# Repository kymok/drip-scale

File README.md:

# drip-scale
A drip scale which measures amount of water added and liquid extracted simultaneously.

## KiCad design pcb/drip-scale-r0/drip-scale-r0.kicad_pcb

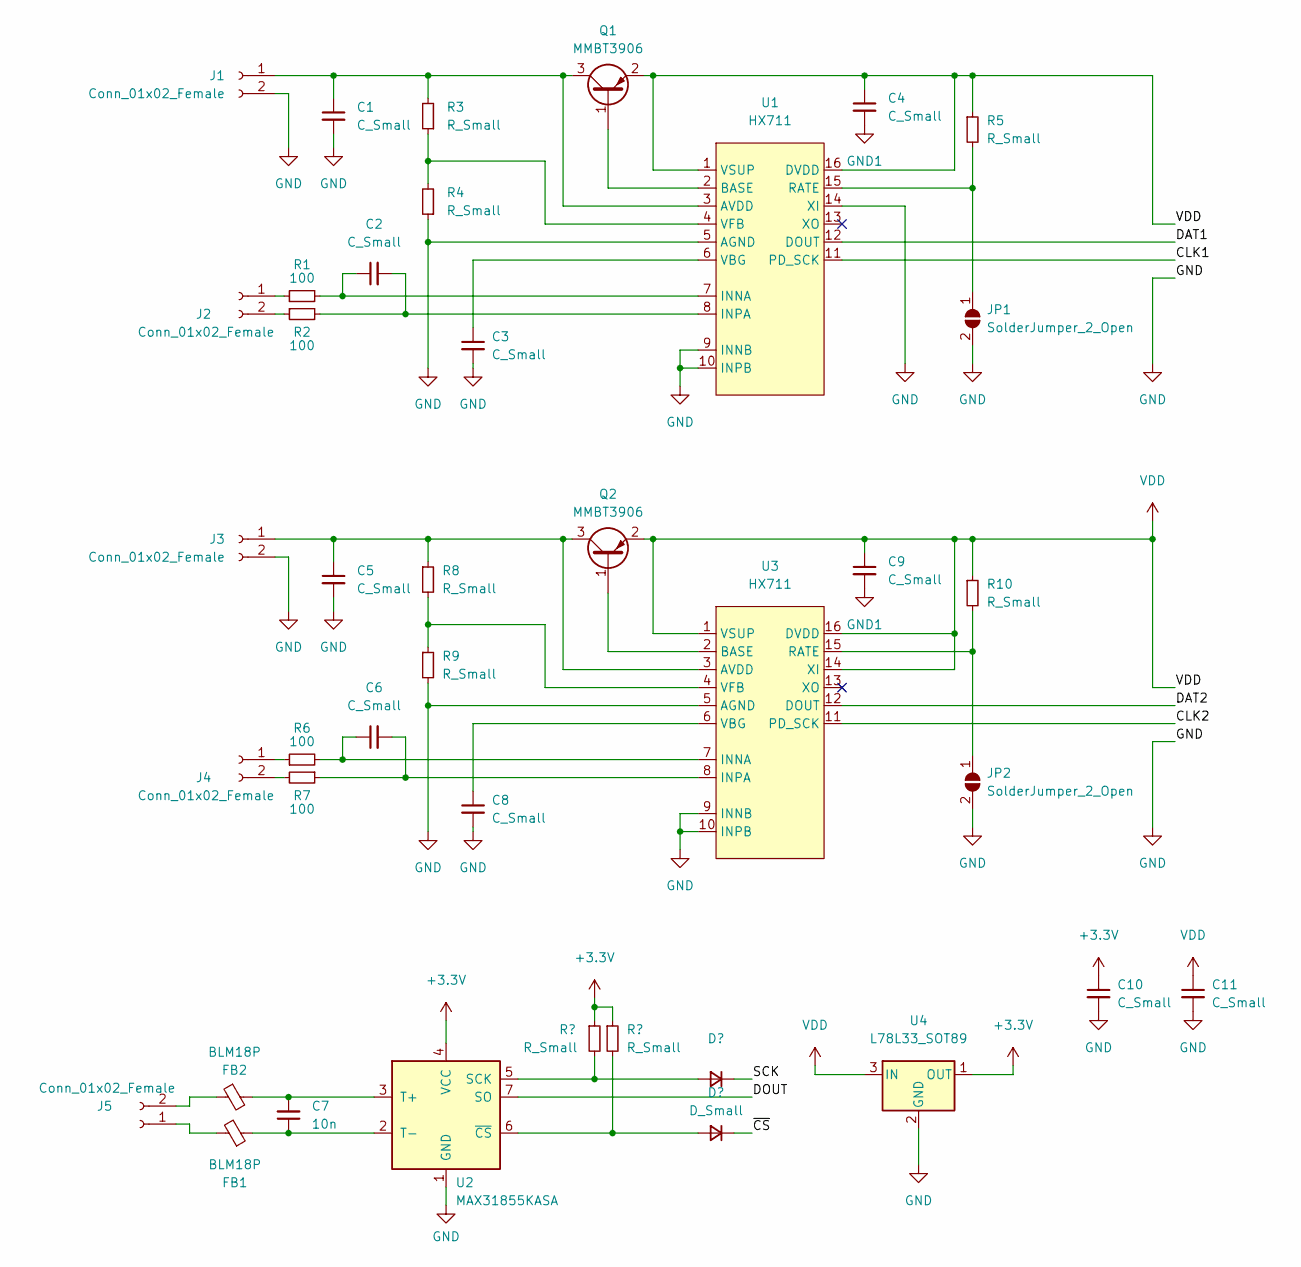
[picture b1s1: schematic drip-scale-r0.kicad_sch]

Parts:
C1, C2, C3, C4, C5, C6, C8, C9, C10, C11: C_Small; C_0603_1608Metric
C7: 10n; C_0603_1608Metric
FB1, FB2: BLM18P; C_0603_1608Metric
J1, J2, J3, J4, J5: Conn_01x02_Female; TerminalBlock_Phoenix_MPT-0,5-2-2.54_1x02_P2.54mm_Horizontal
JP1, JP2: SolderJumper_2_Open; SolderJumper-2_P1.3mm_Open_RoundedPad1.0x1.5mm
Q1, Q2: MMBT3906; SOT-23
R1, R2, R6, R7: 100; R_0603_1608Metric
R3, R4, R5, R8, R9, R10: R_Small; R_0603_1608Metric
U1, U3: HX711; SOP-16_4.4x10.4mm_P1.27mm
U2: MAX31855KASA; SOIC-8_3.9x4.9mm_P1.27mm
U4: L78L33_SOT89; SOT-89-3

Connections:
+3V3: C10.1, U2.4 (VCC), U4.1 (OUT)
/CLK1: U1.11 (PD_SCK)
/CLK2: U3.11 (PD_SCK)
/DAT1: U1.12 (DOUT)
/DAT2: U3.12 (DOUT)
/DOUT: U2.7 (SO)
/SCK: U2.5 (SCK)
/~CS: U2.6 (~CS)
GND: C1.2, C3.2, C5.2, C8.2, C10.2, C11.2, J1.2, J3.2, JP1.2 (B), JP2.2 (B), R4.1, R9.2, U1.5 (AGND), U1.9 (INNB), U1.10 (INPB), U1.14 (XI), U2.1 (GND), U3.5 (AGND), U3.9 (INNB), U3.10 (INPB), U4.2 (GND)
GND1: C4.2, C9.2
unnamed: C1.1, J1.1, Q1.3 (C), R3.2, U1.3 (AVDD)
unnamed: C3.1, U1.6 (VBG)
unnamed: C5.1, J3.1, Q2.3 (C), R8.1, U3.3 (AVDD)
unnamed: C6.1, R6.2, U3.7 (INNA)
unnamed: C6.2, R7.1, U3.8 (INPA)
unnamed: C7.1, FB1.1, U2.2 (T-)
unnamed: C7.2, FB2.2, U2.3 (T+)
unnamed: C8.1, U3.6 (VBG)
unnamed: J2.1, R1.1
unnamed: J2.2, R2.1
unnamed: J4.1, R6.1
unnamed: J4.2, R7.2
unnamed: FB1.2, J5.1
unnamed: FB2.1, J5.2
unnamed: JP1.1 (A), R5.2, U1.15 (RATE)
unnamed: JP2.1 (A), R10.2, U3.15 (RATE)
unnamed: Q1.1 (B), U1.2 (BASE)
unnamed: Q2.1 (B), U3.2 (BASE)
unnamed: C2.1, R1.2, U1.7 (INNA)
unnamed: C2.2, R2.2, U1.8 (INPA)
unnamed: R3.1, R4.2, U1.4 (VFB)
unnamed: R8.2, R9.1, U3.4 (VFB)
VDD: C4.1, C9.1, C11.1, Q1.2 (E), Q2.2 (E), R5.1, R10.1, U1.1 (VSUP), U1.16 (DVDD), U3.1 (VSUP), U3.14 (XI), U3.16 (DVDD), U4.3 (IN)

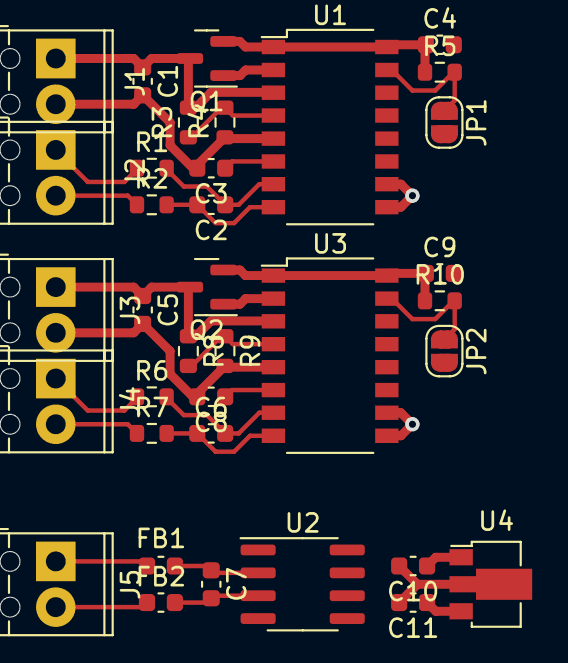
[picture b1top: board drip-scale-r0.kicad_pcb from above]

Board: 2 copper layers, 36 parts (0 on the bottom side), 26 nets.

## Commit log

2022-08-23 Create HX711_usb_serial.ino
    Add arduino code
2022-08-23 Add chassis model
    Add chassis model
2022-08-23 Add serial-webSocket relay
2022-08-23 Add client code
2022-08-24 Add parts to monolithic PCB
2022-08-24 Add module adapter pcb project file
